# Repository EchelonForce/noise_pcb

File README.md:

# Noise PCB

This is a PCB for a Eurorack noise synth module which hosts a Electric Druid Noise2 chip.

Full writeup here: https://www.robotdialogs.com/2022/07/eurorack-noise-generator-v1.html

This work is licensed under a Creative Commons Attribution-NonCommercial-ShareAlike 4.0 International License. https://creativecommons.org/licenses/by-nc-sa/4.0/

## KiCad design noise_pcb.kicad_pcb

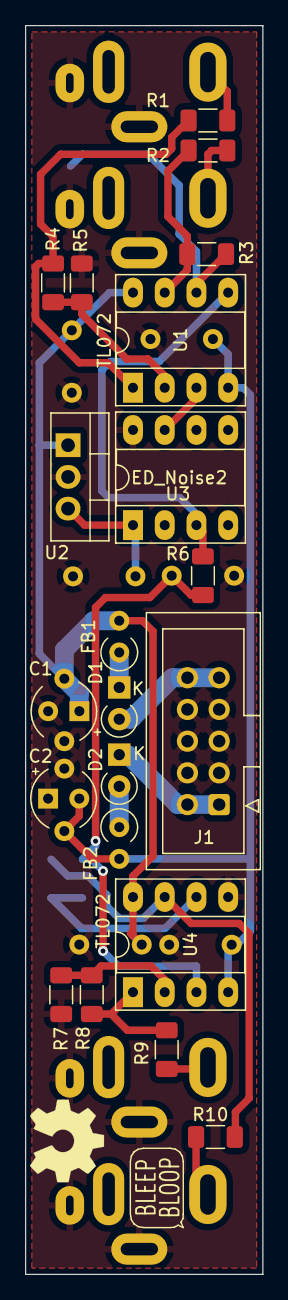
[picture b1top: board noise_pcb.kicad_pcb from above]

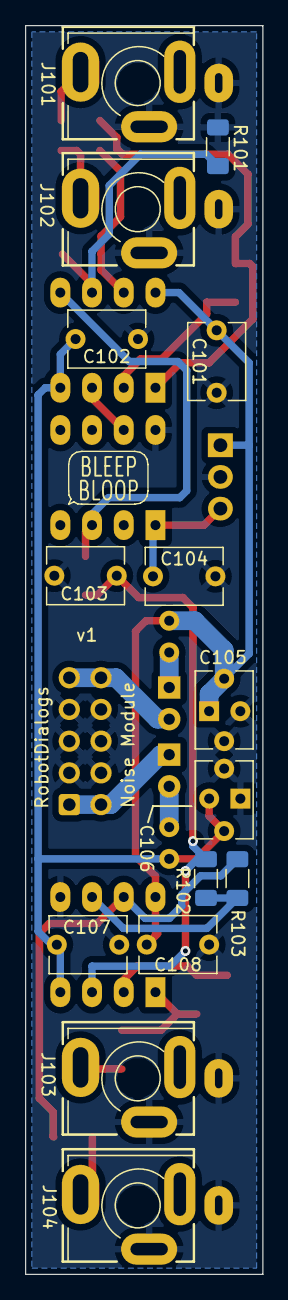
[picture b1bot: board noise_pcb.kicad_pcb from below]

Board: 2 copper layers, 19.0 x 100.0 mm, 39 parts (15 on the bottom side), 23 nets.

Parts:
C1, C2: 100uF; CP_Radial_D5.0mm_P2.50mm
C101, C102, C107, C108: C; C_Disc_D6.0mm_W4.4mm_P5.00mm
C103: 1nF; C_Disc_D6.0mm_W4.4mm_P5.00mm
C104, C105, C106: 10nF; C_Disc_D6.0mm_W4.4mm_P5.00mm
D1, D2: D; D_A-405_P2.54mm_Vertical_KathodeUp
FB1, FB2: FerriteBead; L_Axial_L6.6mm_D2.7mm_P2.54mm_Vertical_Vishay_IM-2
J1: Conn_02x05_Odd_Even; IDC-Header_2x05_P2.54mm_Vertical
J101: PINK_OUT; Jack_3.5mm_MJ-355W_and_PJ398SM_Vertical
J102: WHITE_OUT; Jack_3.5mm_MJ-355W_and_PJ398SM_Vertical
J103: FILT_WHITE; Jack_3.5mm_MJ-355W_and_PJ398SM_Vertical
J104: INV_FILT_WHITE; Jack_3.5mm_MJ-355W_and_PJ398SM_Vertical
LOGO1: logo1; Logo2
LOGO2: Logo_Open_Hardware_Small; OSHW-Symbol_6.7x6mm_SilkScreen
LOGO3: logo1; Logo1
R1, R2, R3, R4, R5, R7, R8, R9, R10, R101: 1k; R_1206_3216Metric_Pad1.30x1.75mm_HandSolder
R6: 5.6k; R_1206_3216Metric_Pad1.30x1.75mm_HandSolder
R102, R103: 100k; R_1206_3216Metric_Pad1.30x1.75mm_HandSolder
U1, U4: TL072; DIP-8_W7.62mm_Socket_LongPads
U2: LM7805_TO220; TO-220-3_Vertical
U3: ElectricDruid_Noise2; DIP-8_W7.62mm_Socket_LongPads

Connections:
+5V: C104.1, U2.3 (VO), U3.1 (+5V)
+12V: C1.1, C101.1, C105.1, C108.1, FB1.2, U1.8 (V+), U2.1 (VI), U4.8 (V+)
+12VA: D1.2 (A), J1.9, J1.10
-12V: C2.2, C102.2, C106.2, C107.2, FB2.2, U1.4 (V-), U4.4 (V-)
-12VA: D2.1 (K), J1.1, J1.2
GND: C1.2, C2.1, C101.2, C102.1, C103.2, C104.2, C105.2, C106.1, C107.1, C108.2, J1.3, J1.4, J1.5, J1.6, J1.7, J1.8, J101.S, J102.S, J103.S, J104.S, R5.1, R7.1, R101.1, U2.2 (GND), U3.8 (GND), U4.5 (+)
unnamed: C103.1, R6.1, R102.1, U4.3 (+)
unnamed: D1.1 (K), FB1.1
unnamed: D2.2 (A), FB2.1
unnamed: J101.T, R1.2
unnamed: J102.T, R2.2
unnamed: J103.T, R9.2
unnamed: J104.T, R10.2
unnamed: R1.1, R4.2, U1.1
unnamed: R3.1, R101.2, U1.6 (-)
unnamed: R2.1, R3.2, U1.7
unnamed: R4.1, R5.2, U1.2 (-)
unnamed: R6.2, U1.5 (+), U3.3 (WHITE_OUT)
unnamed: R7.2, R8.1, U4.2 (-)
unnamed: R8.2, R9.1, U4.1
unnamed: R102.2, R103.1, U4.6 (-)
unnamed: R10.1, R103.2, U4.7
unnamed: U1.3 (+), U3.7 (PINK_OUT)

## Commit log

2022-02-19 Initial commit with .gitignore
2022-02-19 Version 1.0 as ordered
2022-07-10 Assembly notes, value fixes, README
2022-07-10 Title block updates and pdf
